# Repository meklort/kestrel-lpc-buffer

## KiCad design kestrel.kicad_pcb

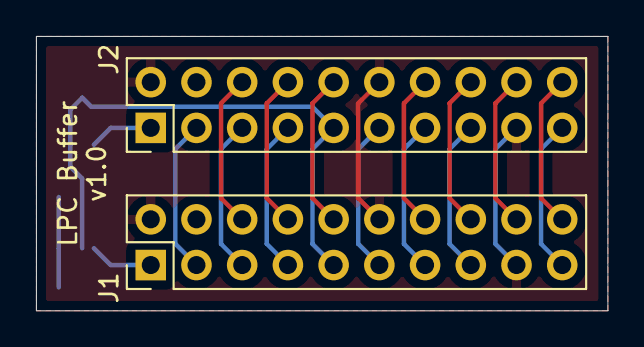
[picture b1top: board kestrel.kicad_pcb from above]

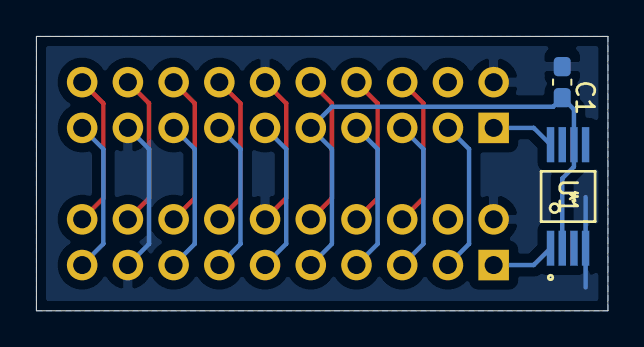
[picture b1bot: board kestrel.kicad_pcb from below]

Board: 2 copper layers, 31.8 x 15.2 mm, 4 parts (2 on the bottom side), 18 nets.

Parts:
C1: 100nF; C_0603_1608Metric_Pad1.08x0.95mm_HandSolder
J1: PPPC102LFBN-RC; PinHeader_2x10_P2.54mm_Vertical
J2: SBH11-PBPC-D10-ST-BK; PinHeader_2x10_P2.54mm_Vertical
U1: LMK1C1102PWR

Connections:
+3.3VP: C1.1, J1.9, J2.9, U1.2, U1.6
+3V3: J1.15, J2.15
/LPC_AD0: J1.11, J2.11
/LPC_AD1: J1.10, J2.10
/LPC_AD2: J1.8, J2.8
/LPC_AD3: J1.7, J2.7
/LPC_CLK: J1.1, U1.1
/LPC_SCL: J1.13, J2.13
/LPC_SDA: J1.14, J2.14
/TPM_GPIO0: J1.20, J2.20
/~LPC_CLKRUN~: J1.18, J2.18
/~LPC_FRAME~: J1.3, J2.3
/~LPC_RESET~: J1.5, J2.5
/~LPC_SERIRQ~: J1.16, J2.16
/~WINDOW_OPEN~: J1.19, J2.19
GND: C1.2, J1.2, J1.12, J1.17, J2.2, J2.12, J2.17, U1.4
unnamed: J1.6, J2.6
unnamed: J2.1, U1.8

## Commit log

2021-05-06 kestrel: Initial LPC buffer board.
